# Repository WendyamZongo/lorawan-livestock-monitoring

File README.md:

# LoRaWAN Livestock Health and Location Monitoring System

An end-to-end LoRaWAN system for monitoring cattle body temperature and location, covering the ear-tag sensor node, the radio link, the gateway, and a real-time web dashboard.

The system is designed for extensive grazing conditions, where animals are dispersed over large areas with no cellular coverage and no mains power, and where a herder cannot practically inspect every animal every day. Early detection of a temperature anomaly and knowledge of an animal's position are the two pieces of information that matter most in that setting.

**Status:** functional prototype. All four subsystems are implemented and working end to end. See Limitations for what is not yet in place.

---

*Real-time herd monitoring dashboard*

*Ear tag node schematic*

*Ear tag node PCB layout*

## System architecture

```
  Ear tag node                    Gateway                    Server
  ------------                    -------                    ------
  ESP32-C6                                                   ChirpStack
  DS18B20  (temperature)   -->    RAK5146 PiHAT       -->    (self-hosted)
  NEO-6M   (GNSS)                 Raspberry Pi                    |
  RFM95W   (LoRa)                                             MQTT
  12,000 mAh Li-ion                                               |
                                                                  v
         LoRaWAN uplink, 4x per day                        Flask dashboard
                                                            + CSV logging
```

---

## Ear tag node

Battery-powered sensor node worn as an ear tag.

| Function | Part |
|---|---|
| MCU | ESP32-C6 |
| Body temperature | DS18B20 (1-Wire) |
| Localisation | u-blox NEO-6M GNSS |
| Radio | RFM95W (LoRa, 868 MHz, SF7) |
| Power | Single 12,000 mAh 3.7 V Li-ion cell |

Firmware is written in C++ using the Arduino framework.

The LoRaWAN ABP uplink path is implemented directly in the firmware, including AES-128 payload encryption and the CMAC-based message integrity check, rather than through a LoRaWAN stack library. This was done to work through the MAC layer explicitly. A production build would use an audited implementation.

### Operating cycle

The node spends almost all of its life in deep sleep. Four times per day it wakes, reads body temperature, acquires a GNSS fix, transmits a single LoRaWAN uplink, and returns to sleep.

Deep sleep on the ESP32-C6 clears RAM and restarts execution from the top, so the entire measurement cycle runs in `setup()` and `loop()` is unused. The LoRaWAN frame counter is held in RTC memory so that it survives sleep; without this the network server would reject every uplink as a replay.

The GNSS receiver is placed in UBX backup mode before sleeping rather than left running. Fix acquisition is bounded by a timeout, and the payload carries a validity flag so the decoder can distinguish a real position from a cycle that ended without a fix. A node under heavy tree cover therefore still reports its temperature instead of draining the cell waiting for satellites.

### Temperature interpretation

The dashboard currently classifies each reading against fixed thresholds: below 35 °C, normal to 38.5 °C, warning to 39.5 °C, and fever above that.

These thresholds are a placeholder, and the limits of the approach are worth stating. The DS18B20 is specified at ±0.5 °C, and an ear tag measures at a site exposed to solar radiation and wind. A fixed cut-off will therefore raise false fever alerts on a hot afternoon and miss real ones at night.

The intended replacement is alerting on sustained deviation from each animal's own baseline, which absorbs both the sensor offset and the individual animal. That logic is not yet implemented.

### Power budget

Sizing assumptions for the 12,000 mAh cell:

| Item | Estimate |
|---|---|
| GNSS fix | ~30 mA for 30 s per cycle |
| LoRa transmit (SF7, 24-byte frame) | ~100 mA for ~60 ms per cycle |
| Sensing and processing | ~40 mA for a few seconds per cycle |
| Deep sleep | board-level quiescent current |
| Cycles per day | 4 |

Transmission is negligible in this budget; the GNSS fix dominates the active cycle. Four cycles per day therefore consume only a few mAh, and on these assumptions the node supports well over two years of operation.

The dominant unknown is board-level quiescent current, not the active cycle. Measuring true sleep current on the assembled board is the single most useful validation step for this figure.

---

## Custom PCB

KiCad design files for the node, including the RFM95W transceiver front-end.

RF layout was the main constraint: ground plane continuity under the transceiver, trace impedance on the antenna feed, antenna placement relative to the enclosure and to the animal's body, and supply decoupling close to the module. The antenna is a soldered helical spring rather than a connectorised u.FL or SMA part, so its position is fixed at assembly and had to be planned around the rest of the layout.

A separate RFM95W breakout board was also designed and fabricated to adapt the module's 2 mm pin pitch to a standard 2.54 mm grid, for bench prototyping and node integration. It carries the module and its pin headers only, and is supplied with regulated 3.3 V from the host board.

Files are in `hardware/`.

---

## Gateway

- **RAK5146 PiHAT Kit** on a Raspberry Pi
- Forwards LoRaWAN uplinks to the network server

Configuration notes are in `gateway/`.

---

## Network server

**ChirpStack**, self-hosted. Handles device provisioning, session keys, deduplication of uplinks received by multiple gateways, and payload decoding.

The device payload decoder is in `chirpstack/`. The uplink carries body temperature, latitude, longitude, and a GNSS validity flag.

---

## Web application

A **Python / Flask** application subscribes to the ChirpStack MQTT broker on the uplink topic for the application, decodes each event, and serves a dashboard showing every device with its latest temperature, its last known position as a Google Maps link, and the time it was last heard from. The page refreshes on a timer, and temperature values are colour-coded by band.

Every uplink is appended to a CSV file, which is the historical record and the export path for offline analysis.

Source is in `webapp/`.

---

## Repository layout

```
firmware/
  Cow_monitoring.ino  ESP32-C6 node firmware (Arduino)
  secrets.h.example   template for LoRaWAN session keys
hardware/
  node/               KiCad schematic and PCB for the ear tag node
  rfm95-breakout/     KiCad files for the RFM95W pitch-adapter board
gateway/              Raspberry Pi + RAK5146 configuration
chirpstack/           payload decoder and device profile
webapp/               Flask dashboard and MQTT subscriber
```

Real LoRaWAN session keys live in `firmware/secrets.h`, which is gitignored. Copy `secrets.h.example` and fill in your own device keys from ChirpStack before flashing.

---

## Limitations

Stated plainly, because they matter to anyone considering this work.

- **Fixed temperature thresholds.** Alerting uses absolute cut-offs rather than a per-animal baseline, which is not adequate for an ear-tag measurement site. See Temperature interpretation above.
- **No database.** History lives in a CSV file. The dashboard itself holds only the latest reading per device in memory, so it is blank after a restart until the next uplink arrives, which may be six hours away.
- **No field validation against a reference.** Temperature readings have not been validated against a rectal or ruminal reference measurement on live animals, which is the standard against which any livestock temperature system must eventually be judged.
- **Battery life is calculated, not measured.** The two-year figure follows from the power budget above. It has not been confirmed by long-duration testing, and board-level sleep current has not yet been measured directly.
- **Hand-rolled cryptography.** The AES-128 and CMAC implementations are the author's own and have not been independently audited. They are appropriate for a prototype, not for a deployed product.
- **NEO-6M cold start.** The module is an older generation with slow cold-start acquisition. Retaining almanac data across wake cycles would reduce time to fix and further improve the energy margin.
- **Single-tag testing.** The system has not been exercised with a herd-scale number of nodes, so airtime contention and duty-cycle behaviour at scale remain untested.

---

## Next steps

- Measure board-level quiescent current and confirm the energy budget empirically
- Replace fixed thresholds with per-animal baseline tracking and deviation-based alerting
- Move from CSV to a time-series database, and reload the dashboard state on restart
- Validate temperature against a reference measurement on live animals
- Test with multiple nodes to characterise airtime and collision behaviour

---

## Author

Wendyam Clovis Dubois Zongo
MSc Electrical Engineering (Computer Engineering), PAUSTI / JKUAT, Nairobi
Embedded systems and FPGA engineer

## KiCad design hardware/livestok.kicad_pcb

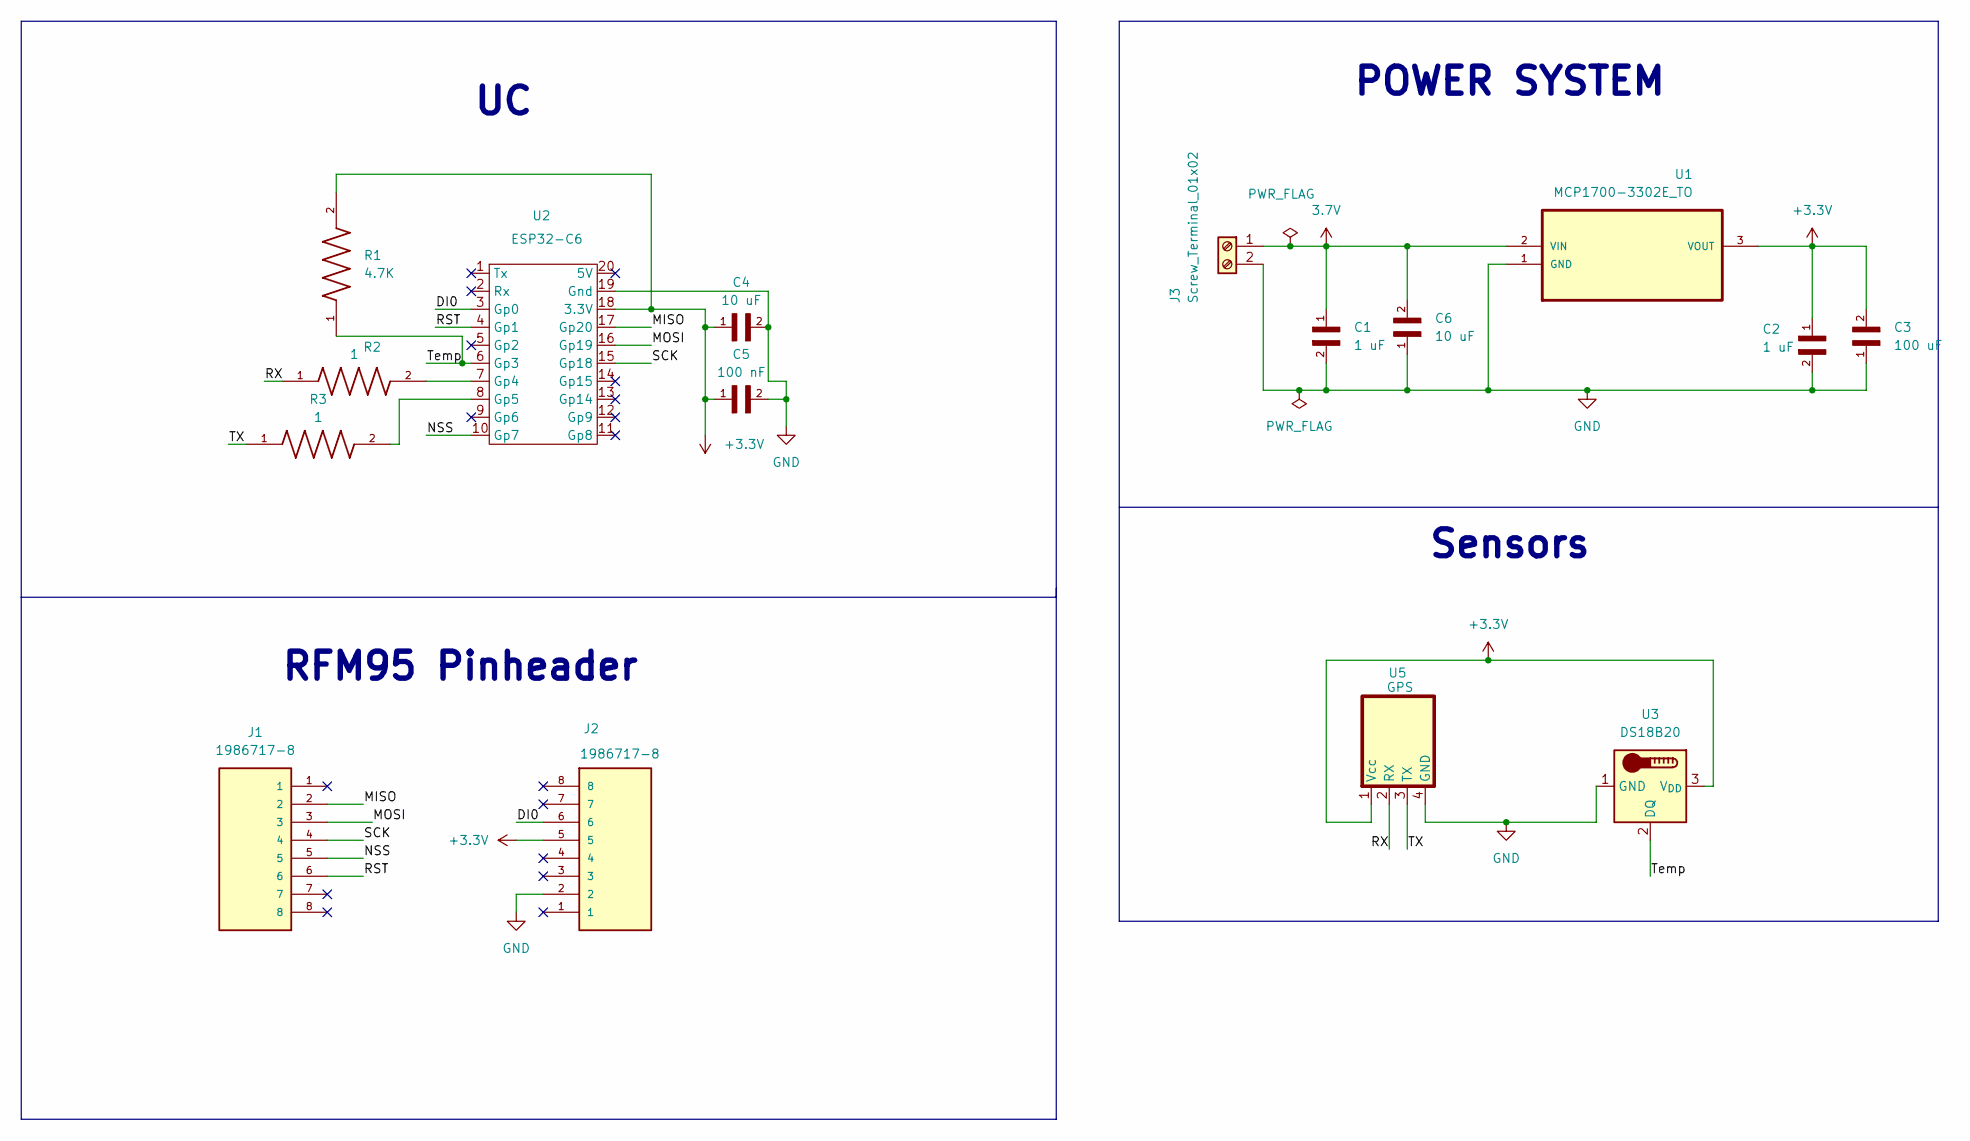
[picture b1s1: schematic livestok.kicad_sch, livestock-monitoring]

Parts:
C1, C2: 1 uF; CAPRB500W50L450T300H550; PARTREV 20200310
C3: 100 uF; CAPRB500W50L450T300H550; PARTREV 20200310
C4, C6: 10 uF; CAPRB500W50L450T300H550; PARTREV 20200310
C5: 100 nF; CAPRB500W50L450T300H550; PARTREV 20200310
J1, J2: 1986717-8; TE_826629-8; PARTREV R
J3: Screw_Terminal_01x02; TerminalBlock_MaiXu_MX126-5.0-02P_1x02_P5.00mm
R1: 4.7K; RESAD1100W55L680D260; PARTREV 201304
R2, R3: 1; RESAD1100W55L680D260; PARTREV 201304
U1: MCP1700-3302E_TO; TO127P254X495-3; MPN MCP1700-3302E/TO
U2: ESP32-C6; C6-mini
U3: DS18B20; TO-92_Inline
U5: GPS; Gps_Yam

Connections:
3.7V: C1.1, C6.2, J3.1, U1.2 (VIN)
+3.3V: C2.1, C3.2, C4.1, C5.1, J2.5, R1.2, U1.3 (VOUT), U2.18 (3.3V), U3.3 (V_{DD}), U5.1 (Vcc)
/DI0: J2.6, U2.3 (Gp0)
/MISO: J1.2, U2.17 (Gp20)
/MOSI: J1.3, U2.16 (Gp19)
/NSS: J1.5, U2.10 (Gp7)
/RST: J1.6, U2.4 (Gp1)
/RX: R2.1, U5.2 (RX)
/SCK: J1.4, U2.15 (Gp18)
/TX: R3.1, U5.3 (TX)
/Temp: R1.1, U2.6 (Gp3), U3.2 (DQ)
GND: C1.2, C2.2, C3.1, C4.2, C5.2, C6.1, J2.2, J3.2, U1.1 (GND), U2.19 (Gnd), U3.1 (GND), U5.4 (GND)
unnamed: R2.2, U2.7 (Gp4)
unnamed: R3.2, U2.8 (Gp5)

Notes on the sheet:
RFM95 Pinheader
POWER SYSTEM
Sensors

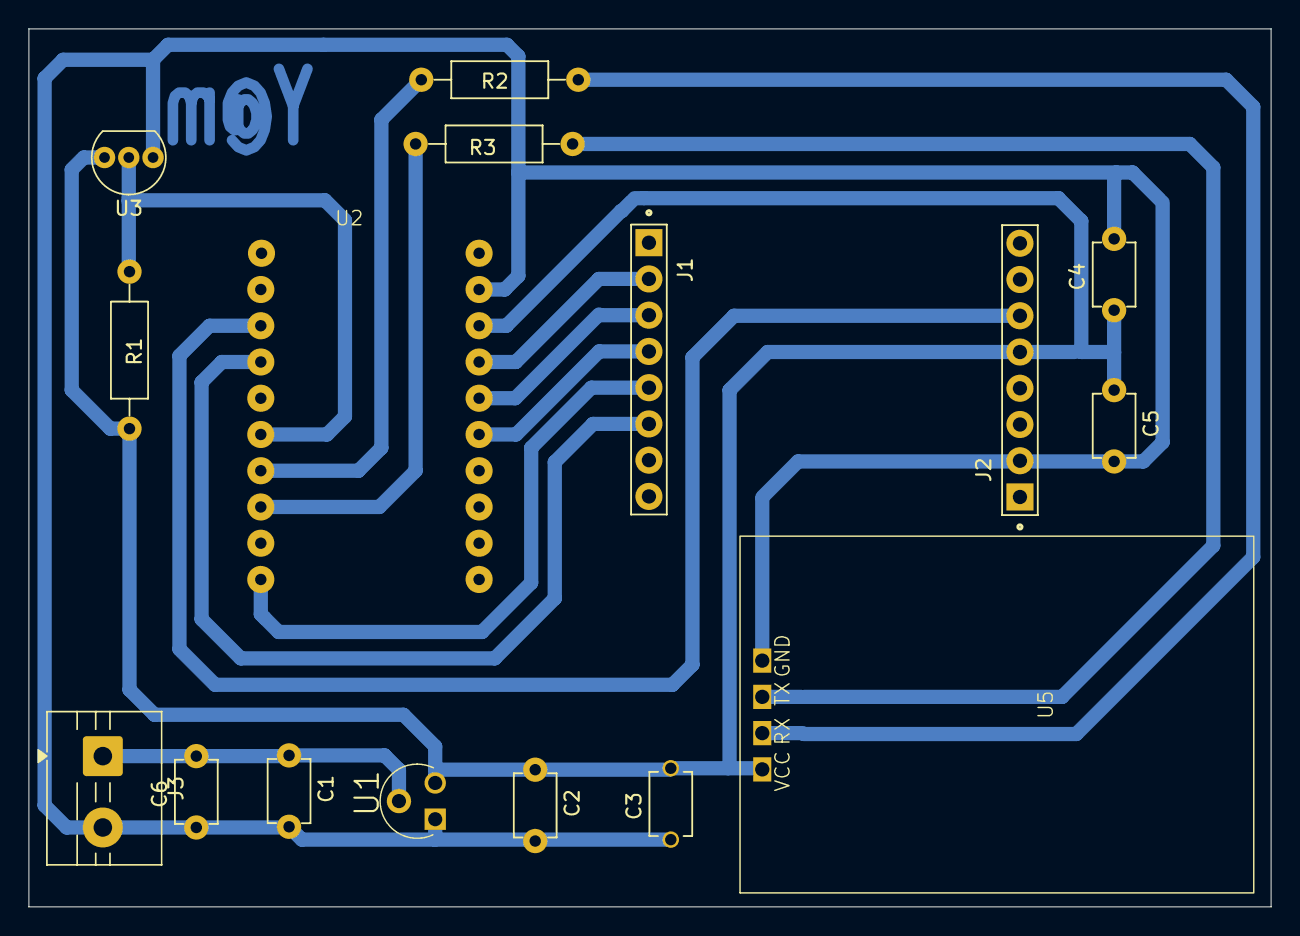
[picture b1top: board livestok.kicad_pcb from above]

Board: 2 copper layers, 87.1 x 61.5 mm, 16 parts (0 on the bottom side), 14 nets.

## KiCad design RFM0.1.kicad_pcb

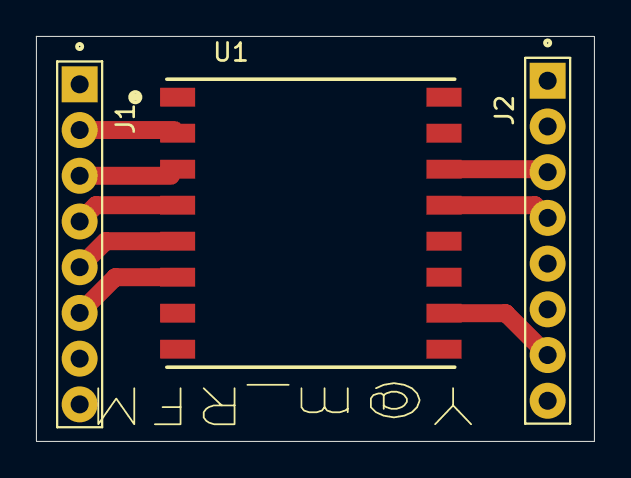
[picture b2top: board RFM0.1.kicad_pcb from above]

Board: 2 copper layers, 31.0 x 22.5 mm, 3 parts (0 on the bottom side), 8 nets.

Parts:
J1, J2: 826629-8; TE_826629-8
U1: RFM95W-868S2; XCVR_RFM95W-868S2

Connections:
/DIO: J2.3, U1.14 (DIO0)
/GND: J2.7, U1.10 (GND@2)
/MOSI: J1.3, U1.3 (MOSI)
unnamed: J1.2, U1.2 (MISO)
unnamed: J1.4, U1.4 (SCK)
unnamed: J1.5, U1.5 (NSS)
unnamed: J1.6, U1.6 (RESET)
unnamed: J2.4, U1.13 (3_3V)
